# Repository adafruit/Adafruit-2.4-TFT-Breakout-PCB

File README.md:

## Adafruit 2.4 TFT Breakout PCB

<a href="http://www.adafruit.com/products/2478"><br/>
Click here to purchase one from the Adafruit shop</a>

PCB files for the Adafruit 2.4" TFT Breakout. Format is EagleCAD schematic and board layout
* https://www.adafruit.com/product/2478

### DESCRIPTION
Add some jazz & pizzazz to your project with a color touchscreen LCD. This TFT display is 2.4" diagonal with a bright (4 white-LED) backlight and it's colorful! 240x320 pixels with individual RGB pixel control, this has way more resolution than a black and white 128x64 display.

As a bonus, this display has a resistive touchscreen attached to it already, so you can detect finger presses anywhere on the screen.

If you need a larger touchscreen, check out the 2.8" diagonal or 3.5" diagonal TFT breakouts. For a smaller display, see our non-touch 2.2" or 1.8" or 1.44" diagonal TFTs

This display has a controller built into it with RAM buffering, so that almost no work is done by the microcontroller. The display can be used in two modes: 8-bit or SPI. For 8-bit mode, you'll need 8 digital data lines and 4 or 5 digital control lines to read and write to the display (12 lines total). SPI mode requires only 5 pins total (SPI data in, data out, clock, select, and d/c) but is slower than 8-bit mode.

In addition, 4 pins are required for the touch screen (2 digital, 2 analog) or you can purchase and use our resistive touchscreen controller (not included) to use I2C or SPI.

### License

Adafruit invests time and resources providing this open source design, please support Adafruit and open-source hardware by purchasing products from [Adafruit.com](https://www.adafruit.com)!

Creative Commons Attribution, Share-Alike license, check license.txt for more information All text above must be included in any redistribution - 
See license.txt for more information.

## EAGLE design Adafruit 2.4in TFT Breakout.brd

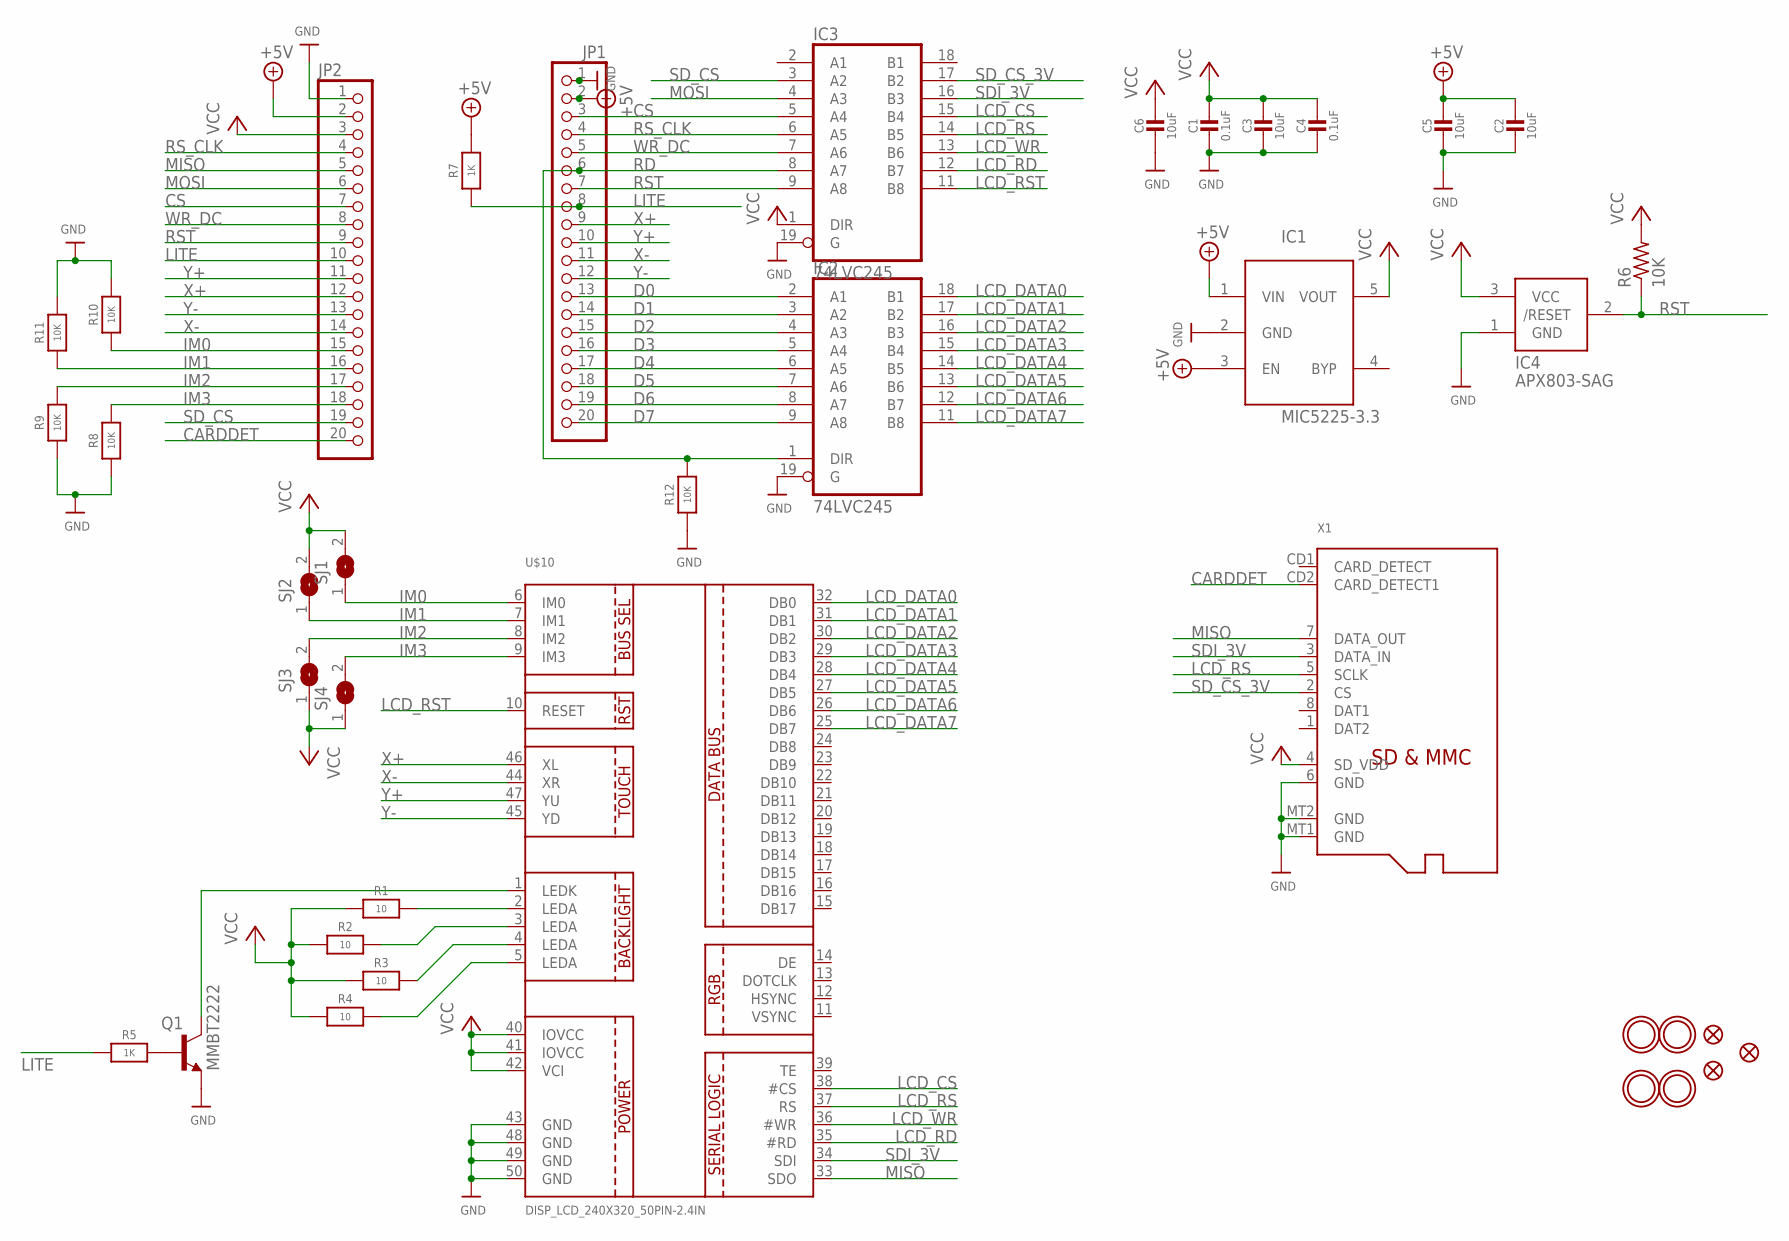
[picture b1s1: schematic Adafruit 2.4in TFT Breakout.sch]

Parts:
C1, C4: 0.1uF; 0805-NO
C2, C3, C5, C6: 10uF; 0805-NO
IC1: MIC5225-3.3; SOT23-5L
IC2, IC3: 74LVC245; SO20W
IC4: APX803-SAG; SOT23
JP1, JP2: HEADER-1X20ROUND; 1X20_ROUND
Q1: MMBT2222; SOT23-BEC
R1, R2, R3, R4: 10; 0805-NO
R5, R7: 1K; 0805-NO
R6: 10K; R0805
R8, R9, R10, R11, R12: 10K; 0805-NO
SJ1, SJ2, SJ3, SJ4: SOLDERJUMPER; SOLDERJUMPER_ARROW_NOPASTE
U$7, U$15, U$16, U$17: MOUNTINGHOLE2.5; MOUNTINGHOLE_2.5_PLATED
U$9, U$11, U$23: FIDUCIAL""; FIDUCIAL_1MM
U$10: DISP_LCD_240X320_50PIN-2.4IN; TFT_2.4IN_240X320_50PIN
X1: MICROSD

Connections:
+3V: C1.1, C3.1, C4.1, C6.1, IC1.5 (VOUT), IC2.20 (VCC), IC3.1 (DIR), IC3.20 (VCC), IC4.3 (VCC), JP2.3, R1.1, R2.1, R3.1, R4.1, R6.2, SJ1.2, SJ2.2, SJ3.1, SJ4.1, U$10.40 (IOVCC), U$10.41 (IOVCC), U$10.42 (VCI), X1.4 (SD_VDD)
CARDDET: JP2.20, X1.CD2 (CARD_DETECT1)
CS: IC3.5 (A4), JP1.3, JP2.7
D0: IC2.2 (A1), JP1.13
D1: IC2.3 (A2), JP1.14
D2: IC2.4 (A3), JP1.15
D3: IC2.5 (A4), JP1.16
D4: IC2.6 (A5), JP1.17
D5: IC2.7 (A6), JP1.18
D6: IC2.8 (A7), JP1.19
D7: IC2.9 (A8), JP1.20
GND: C1.2, C2.2, C3.2, C4.2, C5.2, C6.2, IC1.2 (GND), IC2.10 (GND), IC2.19 (G), IC3.10 (GND), IC3.19 (G), IC4.1 (GND), JP1.1, JP2.1, Q1.E, R8.1, R9.1, R10.2, R11.2, R12.1, U$10.43 (GND), U$10.48 (GND), U$10.49 (GND), U$10.50 (GND), X1.6 (GND), X1.MT1 (GND), X1.MT2 (GND)
IM0: JP2.15, R10.1, SJ1.1, U$10.6 (IM0)
IM1: JP2.16, R11.1, SJ2.1, U$10.7 (IM1)
IM2: JP2.17, R9.2, SJ3.2, U$10.8 (IM2)
IM3: JP2.18, R8.2, SJ4.2, U$10.9 (IM3)
LCD_CS: IC3.15 (B4), U$10.38 (#CS)
LCD_DATA0: IC2.18 (B1), U$10.32 (DB0)
LCD_DATA1: IC2.17 (B2), U$10.31 (DB1)
LCD_DATA2: IC2.16 (B3), U$10.30 (DB2)
LCD_DATA3: IC2.15 (B4), U$10.29 (DB3)
LCD_DATA4: IC2.14 (B5), U$10.28 (DB4)
LCD_DATA5: IC2.13 (B6), U$10.27 (DB5)
LCD_DATA6: IC2.12 (B7), U$10.26 (DB6)
LCD_DATA7: IC2.11 (B8), U$10.25 (DB7)
LCD_RD: IC3.12 (B7), U$10.35 (#RD)
LCD_RS: IC3.14 (B5), U$10.37 (RS), X1.5 (SCLK)
LCD_RST: IC3.11 (B8), U$10.10 (RESET)
LCD_WR: IC3.13 (B6), U$10.36 (#WR)
LITE: JP1.8, JP2.10, R5.1, R7.1
MISO: JP2.5, U$10.33 (SDO), X1.7 (DATA_OUT)
MOSI: IC3.4 (A3), JP2.6
unnamed: R4.2, U$10.5 (LEDA)
unnamed: R1.2, U$10.2 (LEDA)
unnamed: R2.2, U$10.3 (LEDA)
unnamed: R3.2, U$10.4 (LEDA)
unnamed: Q1.C, U$10.1 (LEDK)
unnamed: Q1.B, R5.2
RD: IC2.1 (DIR), IC3.8 (A7), JP1.6, R12.2
RST: IC3.9 (A8), IC4.2 (/RESET), JP1.7, JP2.9, R6.1
RS_CLK: IC3.6 (A5), JP1.4, JP2.4
SDI_3V: IC3.16 (B3), U$10.34 (SDI), X1.3 (DATA_IN)
SD_CS: IC3.3 (A2), JP2.19
SD_CS_3V: IC3.17 (B2), X1.2 (CS)
VIN: C2.1, C5.1, IC1.1 (VIN), IC1.3 (EN), JP1.2, JP2.2, R7.2
WR_DC: IC3.7 (A6), JP1.5, JP2.8
X+: JP1.9, JP2.12, U$10.46 (XL)
X-: JP1.11, JP2.14, U$10.44 (XR)
Y+: JP1.10, JP2.11, U$10.47 (YU)
Y-: JP1.12, JP2.13, U$10.45 (YD)

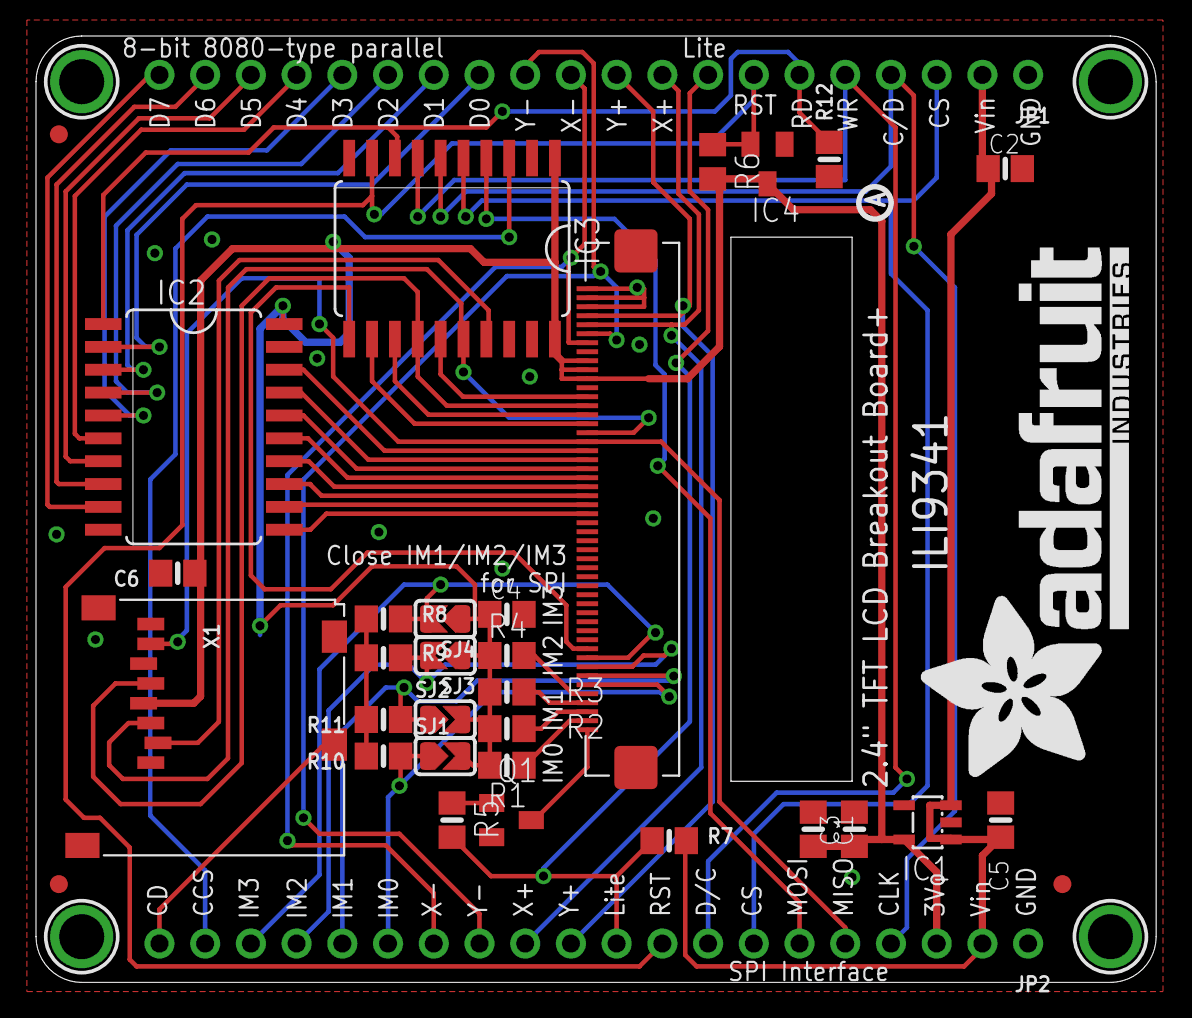
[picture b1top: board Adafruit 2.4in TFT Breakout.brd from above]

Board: 2 copper layers, 62.2 x 52.6 mm, 40 parts (1 on the bottom side), 50 nets.

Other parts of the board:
U$19: ADAFRUIT_TEXT_30MM
U$26: PCBFEAT-REV-040

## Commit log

2016-09-30 init
